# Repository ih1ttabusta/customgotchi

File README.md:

# customgotchi
oh yeah baby tamagotchi time

... but this time serving looks

i made this project because my introduction to hardware was putting a new battery into my old angelgotchi with an iFixit kit and a CR2032 battery i stole from my dad's SNES cartridge repair stash. I got to learn to repair consoles and solder because of that experience.

i'm still really new to hardware, and i figured what better to make than a tamagotchi?

much like a real tamagotchi, you use the three buttons to raise and care for your virtual pet!

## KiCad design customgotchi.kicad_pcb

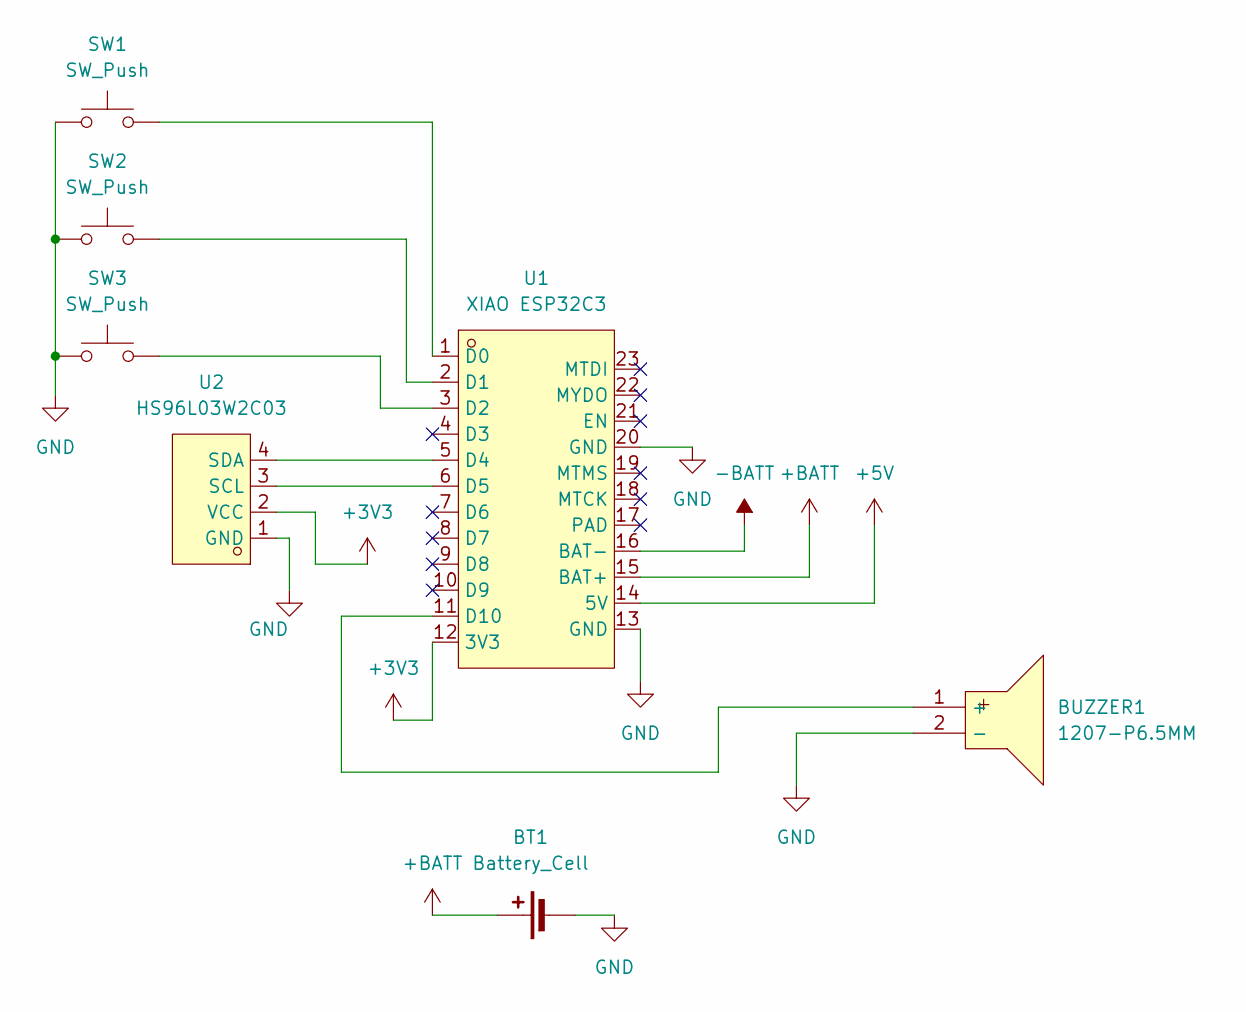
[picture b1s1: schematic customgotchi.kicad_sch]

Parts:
BT1: Battery_Cell; PinHeader_1x02_P2.54mm_Vertical
BUZZER1: 1207-P6.5MM; BUZ-TH_BD12.5-P6.50-D1.4; MPN 1207-P6.5MM; LCSC Part C49246964
SW1, SW2, SW3: SW_Push; SW-TH_4P-L4.5-W4.5-P3.00-LS4.8
U1: XIAO ESP32C3; CONN-SMD_XIAO_ESP32C3; MPN XIAO ESP32C3; LCSC Part C19189385
U2: HS96L03W2C03; OLED-TH_L27.8-W27.2-P2.54_C9900033791; MPN HS96L03W2C03; LCSC Part C5248080

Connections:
+3V3: U1.12 (3V3), U2.2 (VCC)
+5V: U1.14 (5V)
+BATT: BT1.1 (+), U1.15 (BAT+)
-BATT: U1.16 (BAT-)
GND: BT1.2 (-), BUZZER1.2 (-), SW1.1, SW2.1, SW3.1, U1.13 (GND), U1.20 (GND), U2.1 (GND)
unnamed: BUZZER1.1 (+), U1.11 (D10)
unnamed: SW1.2, U1.1 (D0)
unnamed: SW2.2, U1.2 (D1)
unnamed: SW3.2, U1.3 (D2)
unnamed: U1.5 (D4), U2.4 (SDA)
unnamed: U1.6 (D5), U2.3 (SCL)

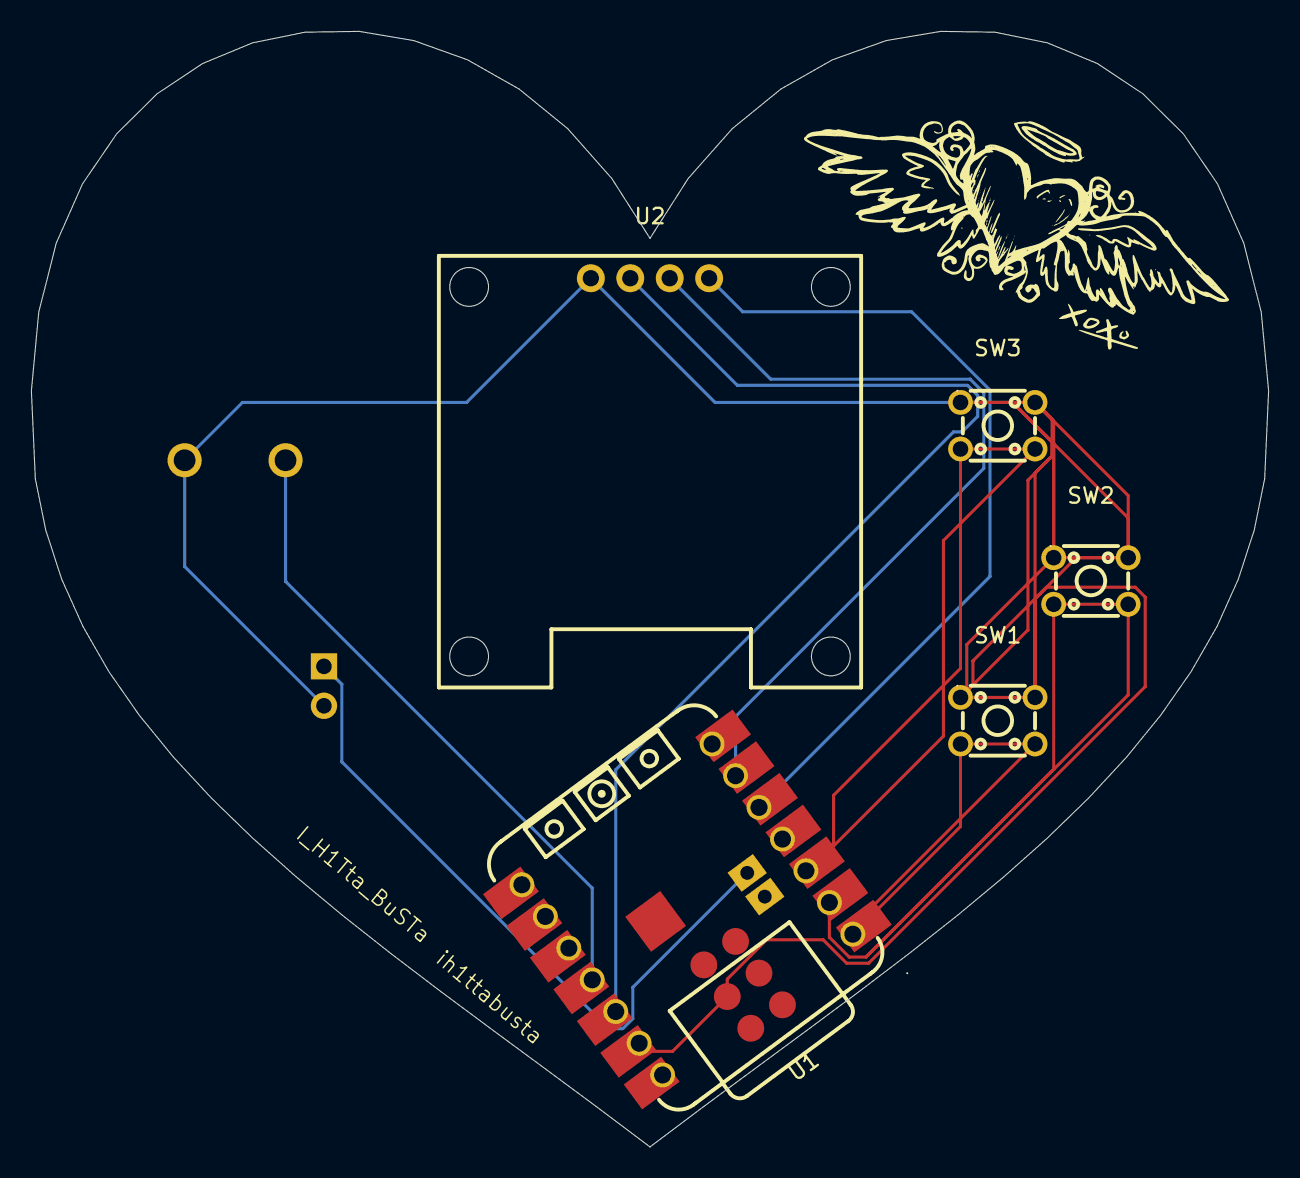
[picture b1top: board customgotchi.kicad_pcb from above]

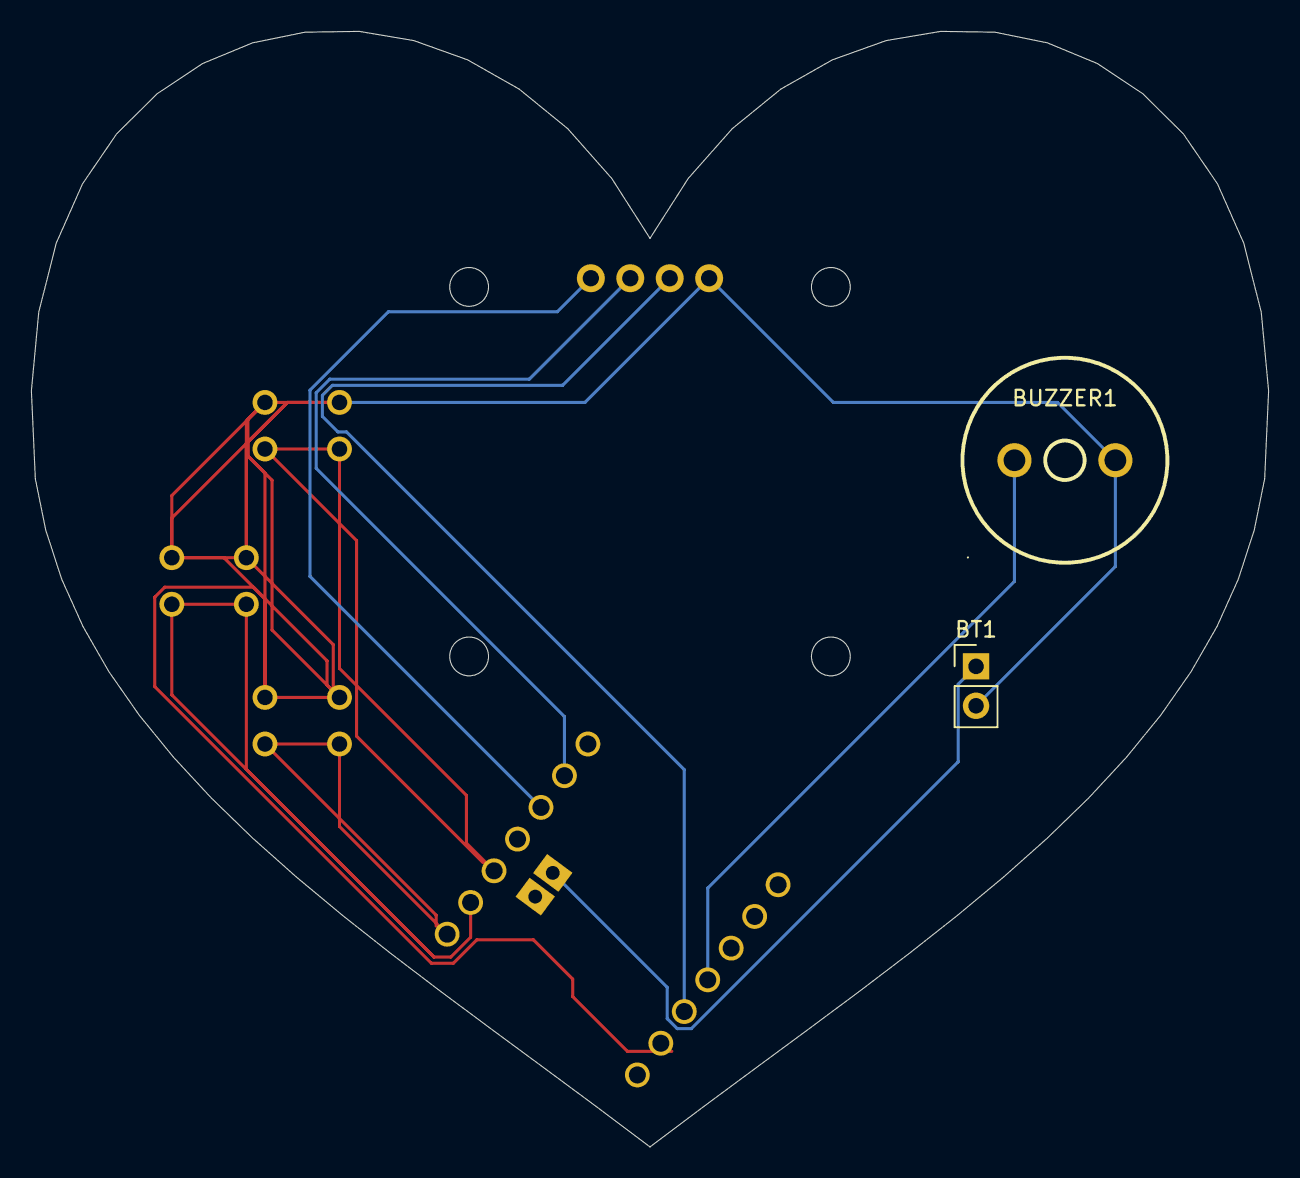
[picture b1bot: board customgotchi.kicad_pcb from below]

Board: 2 copper layers, 79.7 x 71.9 mm, 8 parts (2 on the bottom side), 9 nets.

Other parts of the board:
   : LOGO
